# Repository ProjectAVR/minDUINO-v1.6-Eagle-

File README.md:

# minDUINO-v1.6-Eagle-
A small footprint Arduino Clone, originally designed as an educationl tool.

[Edited text from Projectavr.com]
If you look online you will find a myriad of Arduino™ clones of all different shapes and sizes. So why would I want to produce yet more? I was inspired to create the minDUINO boards because my friend's daughter, I will call her Amelia, had found an interest in electronics. Amelia’s father and I had given her several things to build, commercially available kits, but I wanted to encourage her to experiment. Since I have a familiarity with AVRs and Arduino™, I elected to follow that path.

The minDUINO is designed to be easy to assemble, so it is a two layer through-hole design, and has no SMD components. It has headers for FTDI, ICSP and GPIO breakouts.

The original designs were carried out with EagleCAD.

This repository holds the Eagle files and the final Gerbers which can all be used to create physical boards.

The minDUINO designs are licenced under Creative Commons Attribution-ShareAlike 4.0 International License.

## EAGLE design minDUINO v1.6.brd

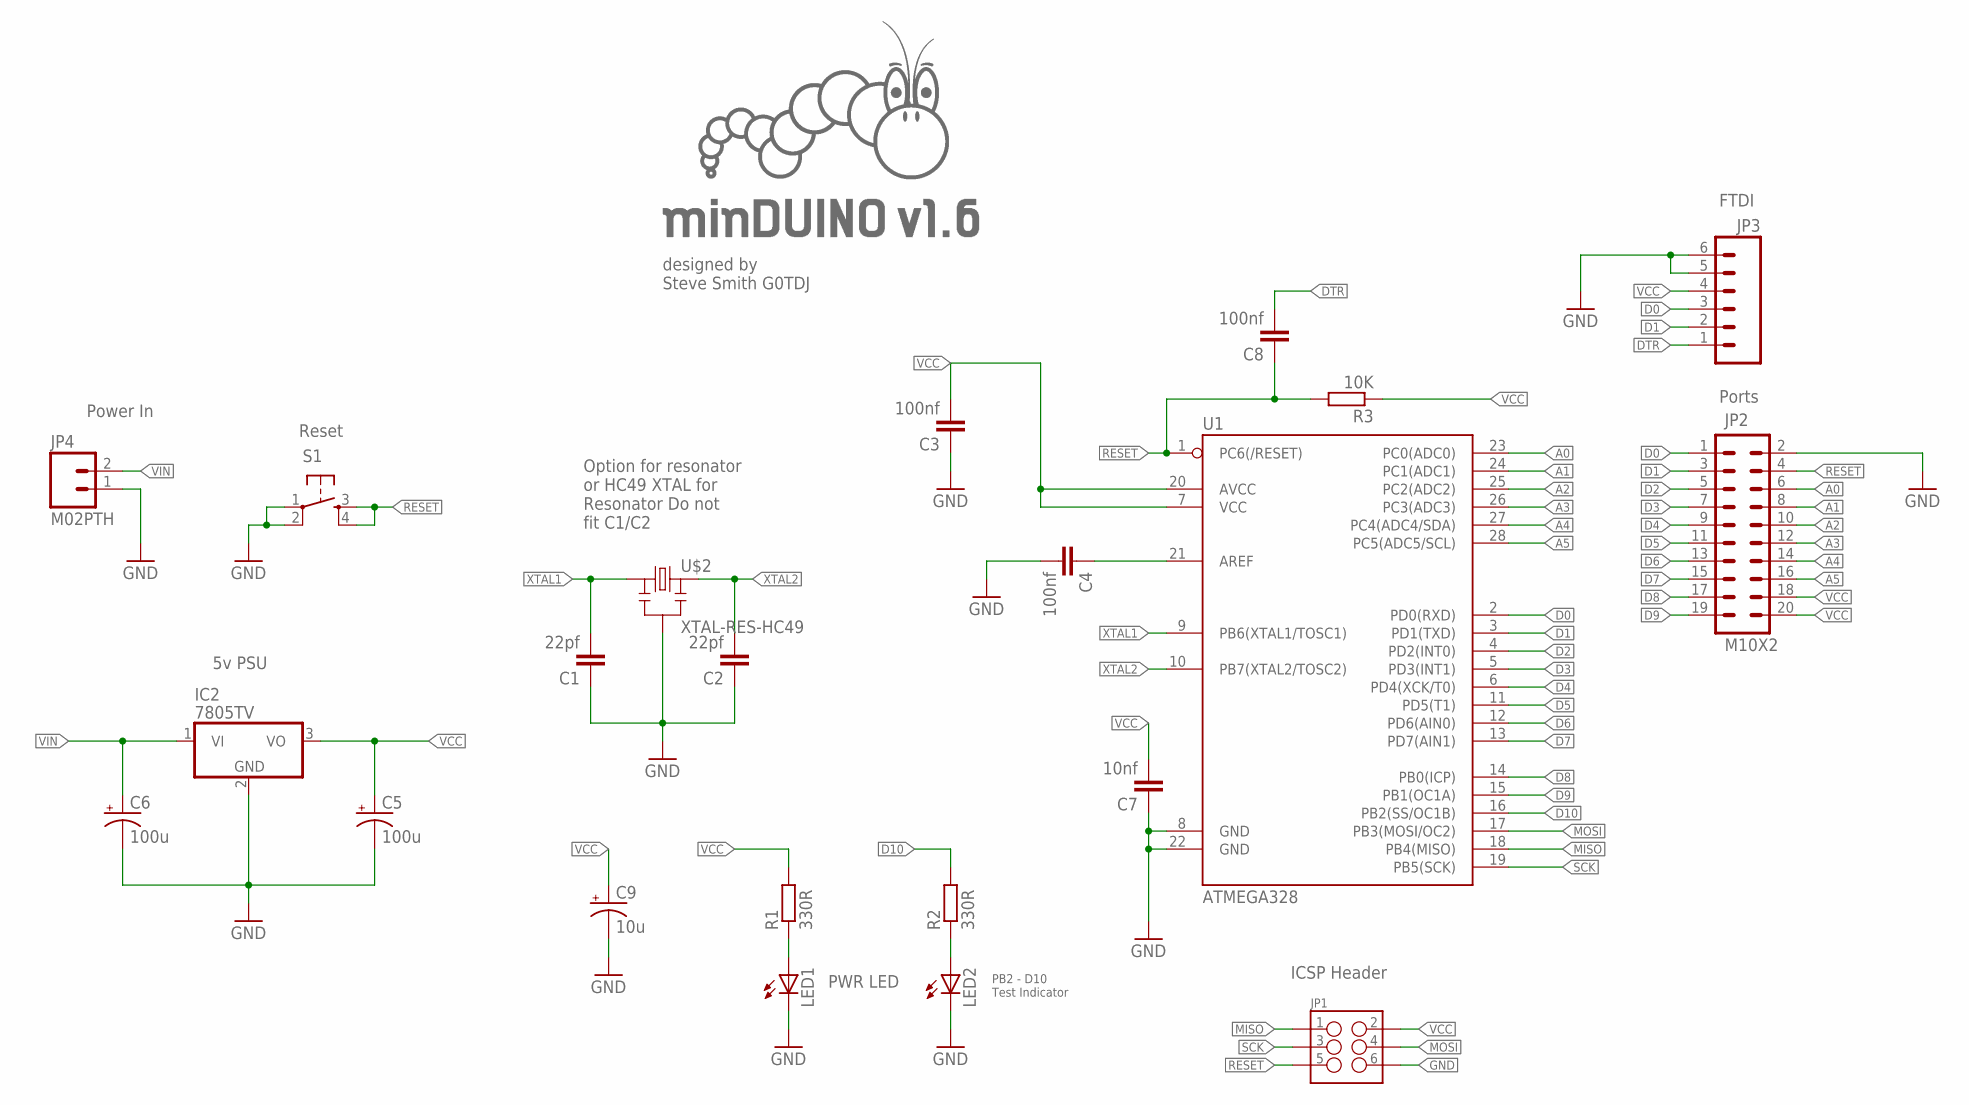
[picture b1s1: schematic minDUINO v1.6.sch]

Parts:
C1, C2: 22pf; C050-030X075
C3, C4, C8: 100nf; C050-030X075
C5, C6: 100u; CPOL-RADIAL-100UF-25V
C7: 10nf; C050-030X075
C9: 10u; CPOL-RADIAL-100UF-25V
IC2: 7805TV; TO220V
JP1: M03X2SHROUD; 2X3-SHROUDED
JP2: M10X2; 2X10
JP3: M06SIP; 1X06
JP4: M02PTH; 1X02
LED1, LED2: LED3MM
R1, R2: 330R; 0411V
R3: 10K; 0411V
S1: TAC_SWITCHPTH; TACTILE-PTH
U1: ATMEGA328; DIL28-3
U$1: MINDUINO_WORDMARK_V1.6
U$2: XTAL-RES-HC49
U$4: MINDUINO_CATERPILLAR

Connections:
A0: JP2.6, U1.23 (PC0(ADC0))
A1: JP2.8, U1.24 (PC1(ADC1))
A2: JP2.10, U1.25 (PC2(ADC2))
A3: JP2.12, U1.26 (PC3(ADC3))
A4: JP2.14, U1.27 (PC4(ADC4/SDA))
A5: JP2.16, U1.28 (PC5(ADC5/SCL))
D0: JP2.1, JP3.3, U1.2 (PD0(RXD))
D1: JP2.3, JP3.2, U1.3 (PD1(TXD))
D2: JP2.5, U1.4 (PD2(INT0))
D3: JP2.7, U1.5 (PD3(INT1))
D4: JP2.9, U1.6 (PD4(XCK/T0))
D5: JP2.11, U1.11 (PD5(T1))
D6: JP2.13, U1.12 (PD6(AIN0))
D7: JP2.15, U1.13 (PD7(AIN1))
D8: JP2.17, U1.14 (PB0(ICP))
D9: JP2.19, U1.15 (PB1(OC1A))
D10: R2.2, U1.16 (PB2(SS/OC1B))
DTR: C8.2, JP3.1
GND: C1.1, C2.1, C3.1, C4.2, C5.2 (-), C6.2 (-), C7.1, C9.2 (-), IC2.2 (GND), JP1.6, JP2.2, JP3.5, JP3.6, JP4.1, LED1.K (C), LED2.K (C), S1.1, S1.2, U1.8 (GND), U1.22 (GND), U$2.2
MISO: JP1.1, U1.18 (PB4(MISO))
MOSI: JP1.4, U1.17 (PB3(MOSI/OC2))
unnamed: LED2.A, R2.1
unnamed: C4.1, U1.21 (AREF)
unnamed: LED1.A, R1.1
RESET: C8.1, JP1.5, JP2.4, R3.2, S1.3, S1.4, U1.1 (PC6(/RESET))
SCK: JP1.3, U1.19 (PB5(SCK))
VCC: C3.2, C5.1 (+), C7.2, C9.1 (+), IC2.3 (VO), JP1.2, JP2.18, JP2.20, JP3.4, R1.2, R3.1, U1.7 (VCC), U1.20 (AVCC)
VIN: C6.1 (+), IC2.1 (VI), JP4.2
XTAL1: C1.2, U1.9 (PB6(XTAL1/TOSC1)), U$2.1
XTAL2: C2.2, U1.10 (PB7(XTAL2/TOSC2)), U$2.3

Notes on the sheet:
PB2 - D10 Test Indicator
designed by Steve Smith G0TDJ
5v PSU
Reset
Power In
ICSP Header
PWR LED
FTDI
Ports
Option for resonator or HC49 XTAL for Resonator Do not fit C1/C2

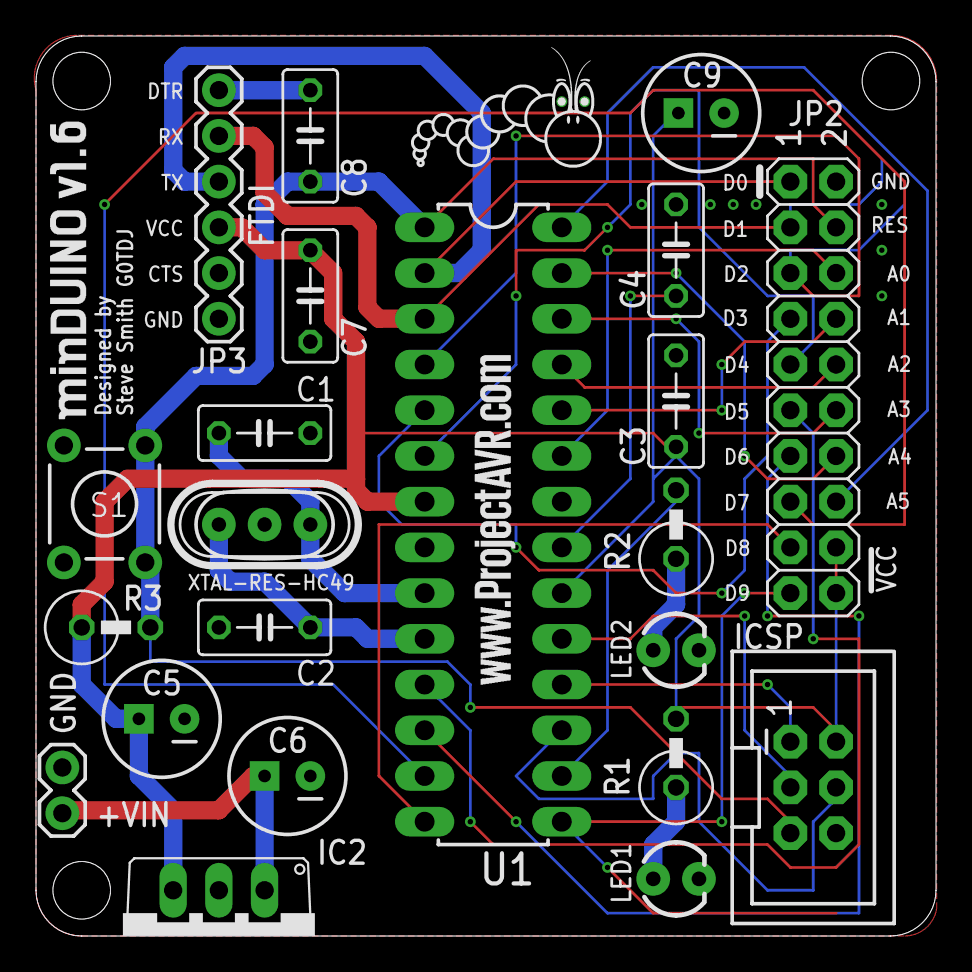
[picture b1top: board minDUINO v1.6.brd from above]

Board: 2 copper layers, 50.0 x 50.0 mm, 26 parts (1 on the bottom side), 30 nets.

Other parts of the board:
U$3, U$5: PROJECTAVR_LOGO_1

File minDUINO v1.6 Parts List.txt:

minDUINO v1.6 Parts List

Assembly variant: 

Part     Value          

C1       22pf
C2       22pf
C3       100nf
C4       100nf
C5       100uf
C6       100uf
C7       10nf
C8       100nf
C9       10uf
IC2      7805 5V  linear Regulator
JP1      Molex Type 2X03 Shrouded Header
JP2      Molex Type 10X02 Header
JP3      Molex Type 1X06 Header
JP4      Molex Type 1x02 Header
LED1   LED3MM  Red
LED2   LED3MM  Green
R1       330R
R2       330R
R3       10K
S1        Tactile Momentary Push Switch
U$2      Low profile HC49 crystal or Resonator (If a resonator is used, do not fit C1/2)
U1       ATMEGA328P

1x 28-Pin 3M/Textool ZIF Socket: 228-3341 (Optional)

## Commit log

2017-01-27 Update README.md
    Added description of the minDUINO boards.
2017-01-27 Update README.md
    Small grammar correction.
2017-01-27 Added Gerbers
2017-01-27 Added Images
2017-01-27 Added Eagle files, schematic and parts list

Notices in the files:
parts and their libraries:
SparkFun-LED: Licensing: CC v3.0 Share-Alike You are welcome to use this library for commercial purposes.
